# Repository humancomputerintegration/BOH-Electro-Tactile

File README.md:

# Full-Hand Electro Tactile Feedback without Obstructing Palmar Side of Hand

This is the repository for PCB schematics and Arduino codes used for the "Full-Hand Electro Tactile Feedback without Obstructing Palmar Side of Hand" paper (ACM CHI2023).

For more information, please refer to our paper: http://lab.plopes.org/#boh-electro-tactile

## notes:
1.	For PCB, the design originally assumes the use of the Bluetooth Module + Lipo battery but also works with normal Serial + power via Seeeduino XIAO's USB-C. If you go for this tethered option, ensure the battery is not connected, the power switch on the PCB is toggled ON, and the Bluetooth module is removed.
2.	The Kicad project for the PCB has not been tested for library compatibility, so let us know if it does not appear properly on your end, but just uploading the Gerber file should suffice for ordering the PCB.
3.	The Arduino code is a generic program to drive the circuit in response to Serial messages from other program instances such as Unity, Python, Processing, etc.

# citing
When using or building upon this device in an academic publication, please consider citing as follows:

Yudai Tanaka, Alan Shen, Andy Kong, and Pedro Lopes. 2023. Full-Hand Electro-Tactile Feedback without Obstructing Palmar Side of Hand. In Proceedings of the 2023 CHI Conference on Human Factors in Computing Systems (CHI'23), April 23-28, 2023, Hamburg, Germany. ACM, NewYork, NY, USA, 15 pages. https://dl.acm.org/doi/abs/10.1145/3544548.3581382

# contact
For any questions about this repository, please contact yudaitanaka@uchicago.edu

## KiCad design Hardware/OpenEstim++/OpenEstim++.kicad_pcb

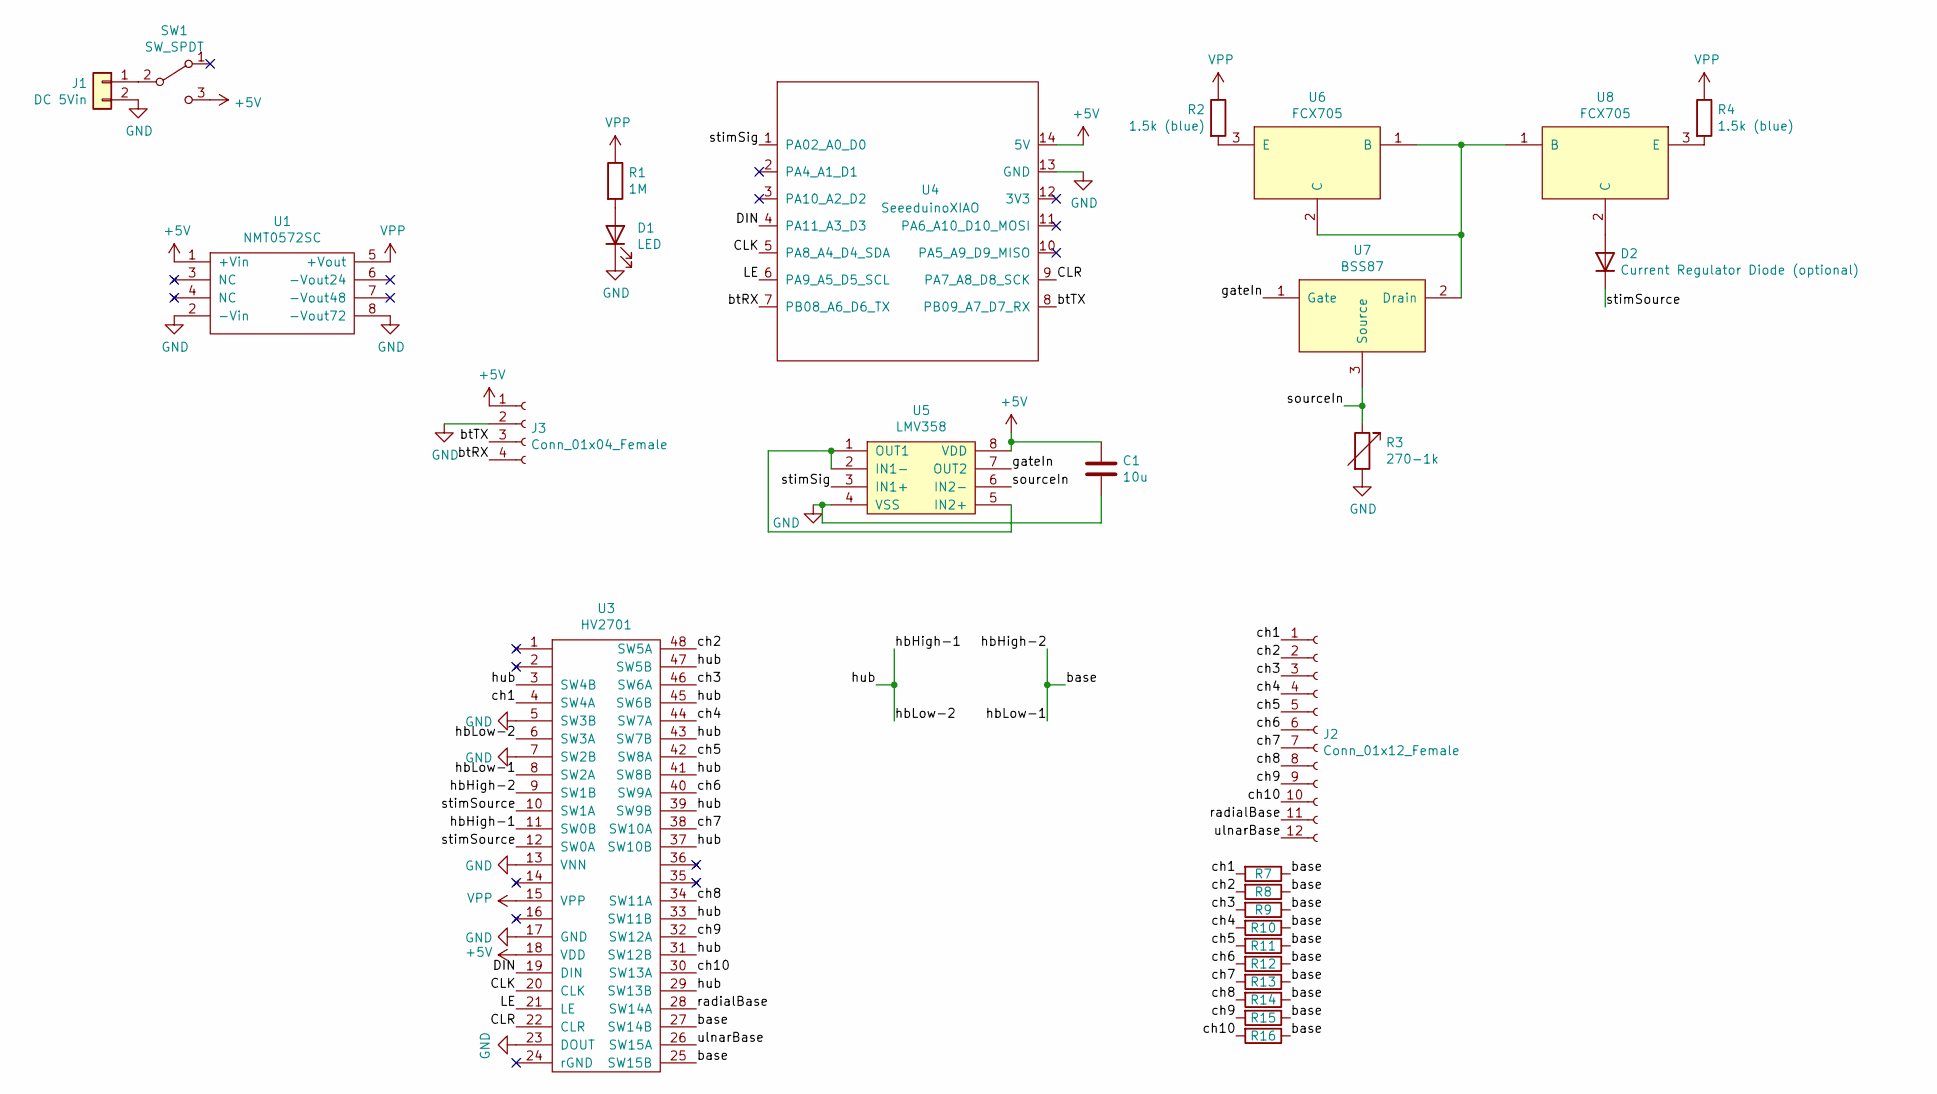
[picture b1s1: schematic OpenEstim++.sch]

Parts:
C1: 10u; C_1210_HandSoldering
D1: LED; LED_0603_HandSoldering
D2: Current Regulator Diode (optional); Pin_Header_Straight_1x02_Pitch2.54mm
J1: DC 5Vin; Pin_Header_Straight_1x02_Pitch2.54mm
J2: Conn_01x12_Female; Pin_Header_Straight_1x12_Pitch2.54mm
J3: Conn_01x04_Female; Pin_Header_Straight_1x04_Pitch2.54mm
R1: 1M; R_0805_HandSoldering
R2, R4: 1.5k (blue); R_0805_HandSoldering
R3: 270-1k; R_0805_HandSoldering
R7, R8, R9, R10, R11, R12, R13, R14, R15, R16: R; R_0805_HandSoldering
SW1: SW_SPDT; Pin_Header_Straight_1x03_Pitch2.00mm
U1: NMT0572SC
U3: HV2701; LQFP-48_7x7mm_Pitch0.5mm
U4: SeeeduinoXIAO; seeeduinoXiao
U5: LMV358; MSOP-8_3x3mm_Pitch0.65mm
U6, U8: FCX705; SOT-89-3_Handsoldering
U7: BSS87; SOT-89-3_Handsoldering

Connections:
+5V: C1.1, J3.1, SW1.3 (C), U1.1 (+Vin), U3.18 (VDD), U4.14 (5V), U5.8 (VDD)
/CLK: U3.20 (CLK), U4.5 (PA8_A4_D4_SDA)
/CLR: U3.22 (CLR), U4.9 (PA7_A8_D8_SCK)
/DIN: U3.19 (DIN), U4.4 (PA11_A3_D3)
/LE: U3.21 (LE), U4.6 (PA9_A5_D5_SCL)
/base: R7.1, R8.1, R9.1, R10.1, R11.1, R12.1, R13.1, R14.1, R15.1, R16.1, U3.8 (SW2A), U3.9 (SW1B), U3.25 (SW15B), U3.27 (SW14B)
/btRX: J3.4, U4.7 (PB08_A6_D6_TX)
/btTX: J3.3, U4.8 (PB09_A7_D7_RX)
/ch1: J2.1, R7.2, U3.4 (SW4A)
/ch2: J2.2, R8.2, U3.48 (SW5A)
/ch3: J2.3, R9.2, U3.46 (SW6A)
/ch4: J2.4, R10.2, U3.44 (SW7A)
/ch5: J2.5, R11.2, U3.42 (SW8A)
/ch6: J2.6, R12.2, U3.40 (SW9A)
/ch7: J2.7, R13.2, U3.38 (SW10A)
/ch8: J2.8, R14.2, U3.34 (SW11A)
/ch9: J2.9, R15.2, U3.32 (SW12A)
/ch10: J2.10, R16.2, U3.30 (SW13A)
/gateIn: U5.7 (OUT2), U7.1 (Gate)
/hbHigh-1: U3.3 (SW4B), U3.6 (SW3A), U3.11 (SW0B), U3.29 (SW13B), U3.31 (SW12B), U3.33 (SW11B), U3.37 (SW10B), U3.39 (SW9B), U3.41 (SW8B), U3.43 (SW7B), U3.45 (SW6B), U3.47 (SW5B)
/radialBase: J2.11, U3.28 (SW14A)
/sourceIn: R3.1, U5.6 (IN2-), U7.3 (Source)
/stimSig: U4.1 (PA02_A0_D0), U5.3 (IN1+)
/stimSource: D2.1 (K), U3.10 (SW1A), U3.12 (SW0A)
/ulnarBase: J2.12, U3.26 (SW15A)
GND: C1.2, D1.1 (K), J1.2, J3.2, R3.2, U1.2 (-Vin), U1.8 (-Vout72), U3.5 (SW3B), U3.7 (SW2B), U3.13 (VNN), U3.17 (GND), U3.23 (DOUT), U4.13 (GND), U5.4 (VSS)
unnamed: D1.2 (A), R1.2
unnamed: D2.2 (A), U8.2 (C)
unnamed: J1.1, SW1.2 (B)
unnamed: R2.2, U6.3 (E)
unnamed: R4.2, U8.3 (E)
unnamed: U5.1 (OUT1), U5.2 (IN1-), U5.5 (IN2+)
unnamed: U6.1 (B), U6.2 (C), U7.2 (Drain), U8.1 (B)
VPP: R1.1, R2.1, R4.1, U1.5 (+Vout), U3.15 (VPP)

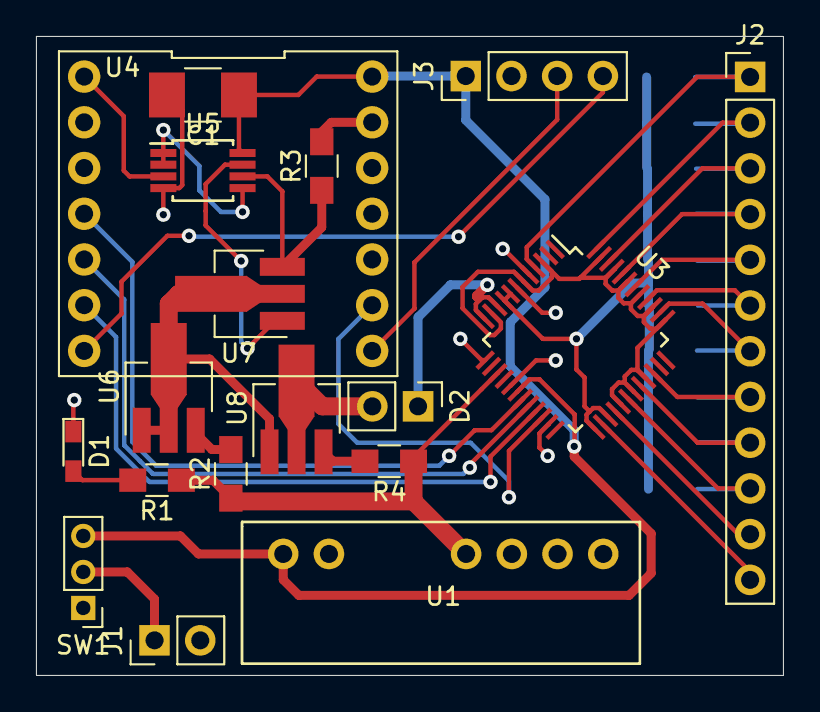
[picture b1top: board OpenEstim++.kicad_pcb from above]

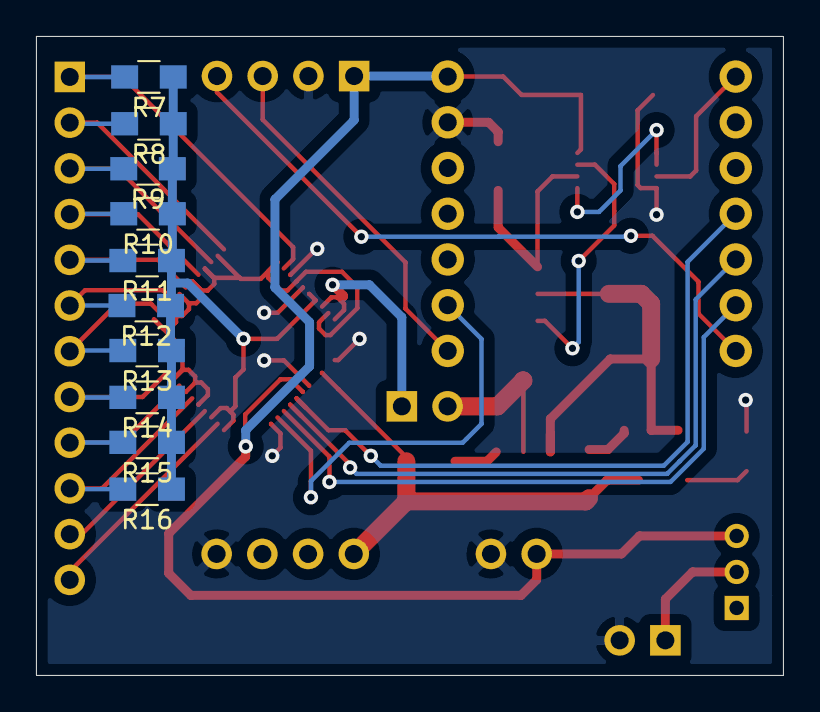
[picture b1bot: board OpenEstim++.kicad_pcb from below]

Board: 2 copper layers, 41.5 x 35.5 mm, 28 parts (10 on the bottom side), 34 nets.
